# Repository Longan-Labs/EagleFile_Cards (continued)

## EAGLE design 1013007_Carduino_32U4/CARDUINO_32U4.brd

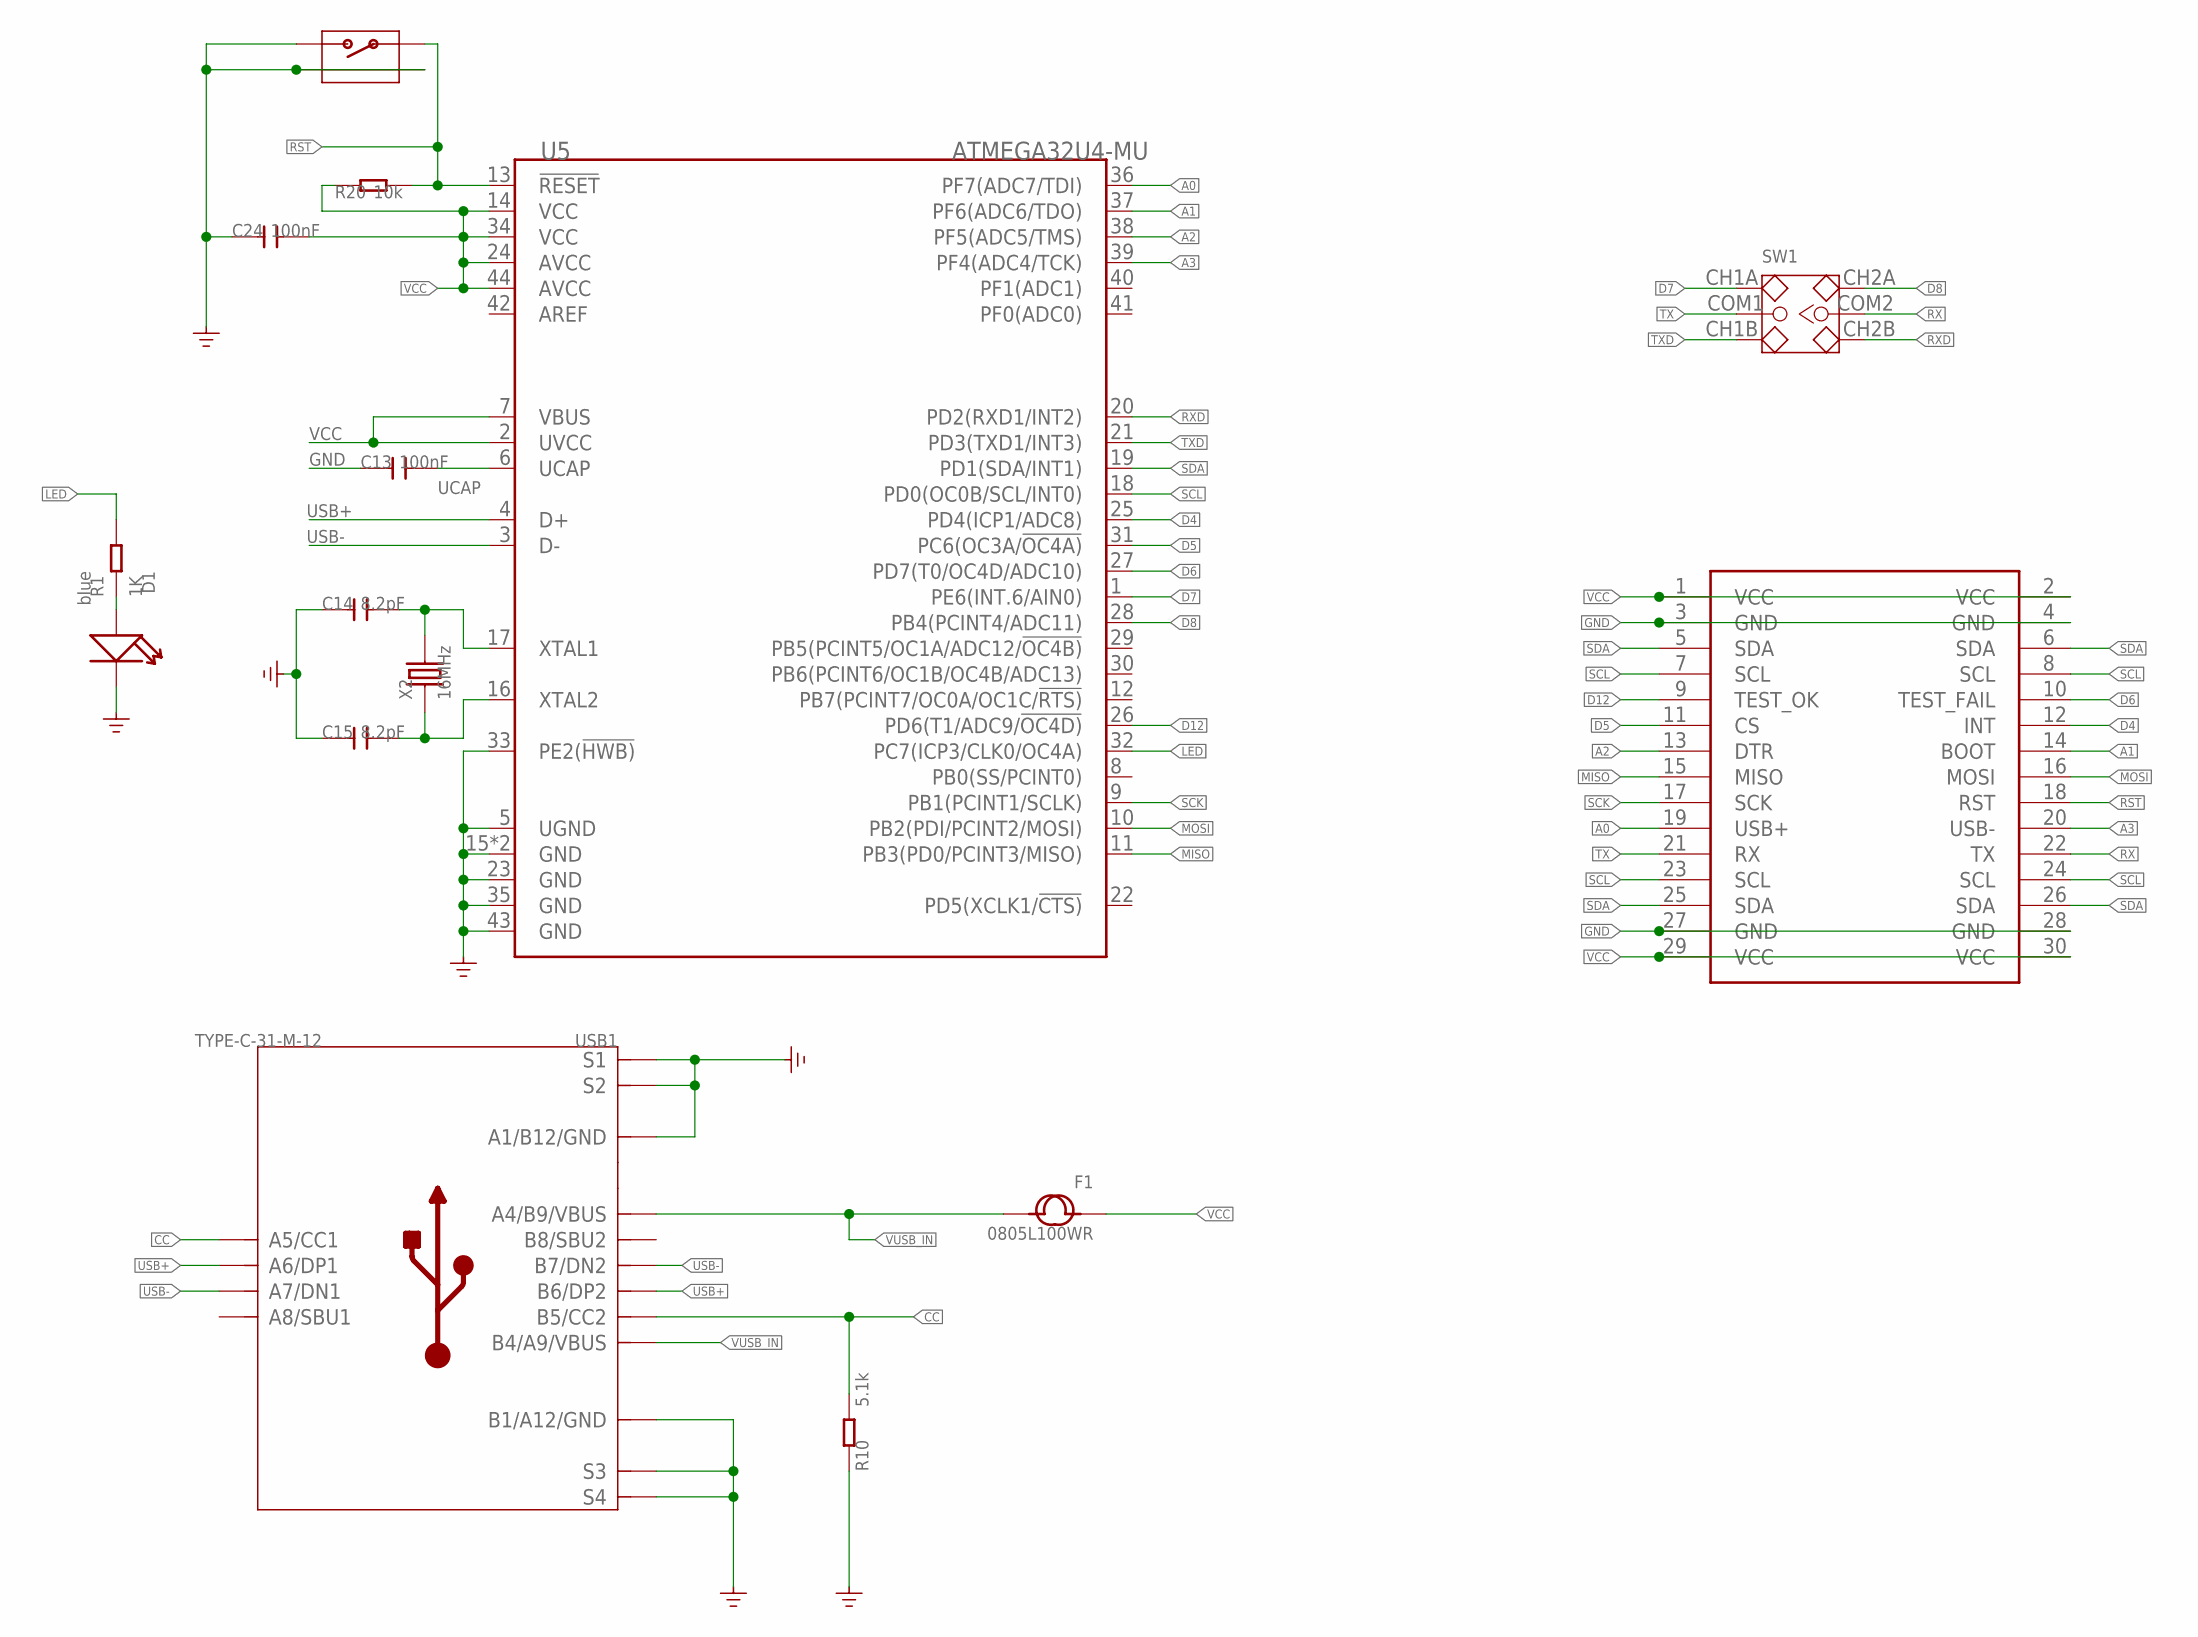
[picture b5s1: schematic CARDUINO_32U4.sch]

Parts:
C13, C24: 100nF; C0603
C14, C15: 8.2pF; C0603
D1: blue; LED-0603
F1: 0805L100WR; F0805
MOUDLE1: MOUDLE-2X15P-2.54'BOARD'; MOUDLE-2X15P-2.54
R1: 1K; R0603
R10: 5.1k; R0603
R20: 10k; R0603
RESET: BUTTON-4P-REINFORCE; 4P-SMD-7X3.5X3.5H
SW1: SWITCH-2CH-6P; SW6-2.5-SMD-9.2X3.5X3.5MM
U5: ATMEGA32U4-MU; QFN44
USB1: TYPE-C-31-M-12; USB2.0-TYPE-C
X2: 16MHz; 2P-SMD-5X3.2

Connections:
A0: MOUDLE1.19 (USB+), U5.36 (PF7(ADC7/TDI))
A1: MOUDLE1.14 (BOOT), U5.37 (PF6(ADC6/TDO))
A2: MOUDLE1.13 (DTR), U5.38 (PF5(ADC5/TMS))
A3: MOUDLE1.20 (USB-), U5.39 (PF4(ADC4/TCK))
CC: R10.2, USB1.A5 (A5/CC1), USB1.B5 (B5/CC2)
D4: MOUDLE1.12 (INT), U5.25 (PD4(ICP1/ADC8))
D5: MOUDLE1.11 (CS), U5.31 (PC6(OC3A/!OC4A))
D6: MOUDLE1.10 (TEST_FAIL), U5.27 (PD7(T0/OC4D/ADC10))
D7: SW1.CH1A, U5.1 (PE6(INT.6/AIN0))
D8: SW1.CH2A, U5.28 (PB4(PCINT4/ADC11))
D12: MOUDLE1.9 (TEST_OK), U5.26 (PD6(T1/ADC9/!OC4D))
GND: C13.1, C14.1, C15.1, C24.1, D1.-, MOUDLE1.3 (GND), MOUDLE1.4 (GND), MOUDLE1.27 (GND), MOUDLE1.28 (GND), R10.1, RESET.2, RESET.S1, RESET.S2, U5.5 (UGND), U5.15 (GND), U5.23 (GND), U5.33 (PE2(!HWB)), U5.35 (GND), U5.43 (GND), U5.TAB (GND), USB1.A1_B12 (A1/B12/GND), USB1.B1_A12 (B1/A12/GND), USB1.S1, USB1.S2, USB1.S3, USB1.S4, USB1.S5 (S1), USB1.S6 (S2)
LED: R1.2, U5.32 (PC7(ICP3/CLK0/OC4A))
MISO: MOUDLE1.15 (MISO), U5.11 (PB3(PD0/PCINT3/MISO))
MOSI: MOUDLE1.16 (MOSI), U5.10 (PB2(PDI/PCINT2/MOSI))
unnamed: D1.+, R1.1
unnamed: C14.2, U5.17 (XTAL1), X2.2
unnamed: C15.2, U5.16 (XTAL2), X2.1
RST: MOUDLE1.18 (RST), R20.2, RESET.1, U5.13 (!RESET)
RX: MOUDLE1.22 (TX), SW1.COM2
RXD: SW1.CH2B, U5.20 (PD2(RXD1/INT2))
SCK: MOUDLE1.17 (SCK), U5.9 (PB1(PCINT1/SCLK))
SCL: MOUDLE1.7 (SCL), MOUDLE1.8 (SCL), MOUDLE1.23 (SCL), MOUDLE1.24 (SCL), U5.18 (PD0(OC0B/SCL/INT0))
SDA: MOUDLE1.5 (SDA), MOUDLE1.6 (SDA), MOUDLE1.25 (SDA), MOUDLE1.26 (SDA), U5.19 (PD1(SDA/INT1))
TX: MOUDLE1.21 (RX), SW1.COM1
TXD: SW1.CH1B, U5.21 (PD3(TXD1/INT3))
UCAP: C13.2, U5.6 (UCAP)
USB+: U5.4 (D+), USB1.A6 (A6/DP1), USB1.B6 (B6/DP2)
USB-: U5.3 (D-), USB1.A7 (A7/DN1), USB1.B7 (B7/DN2)
VCC: C24.2, F1.1, MOUDLE1.1 (VCC), MOUDLE1.2 (VCC), MOUDLE1.29 (VCC), MOUDLE1.30 (VCC), R20.1, U5.2 (UVCC), U5.7 (VBUS), U5.14 (VCC), U5.24 (AVCC), U5.34 (VCC), U5.44 (AVCC)
VUSB_IN: F1.2, USB1.A4_B9 (A4/B9/VBUS), USB1.B4_A9 (B4/A9/VBUS)

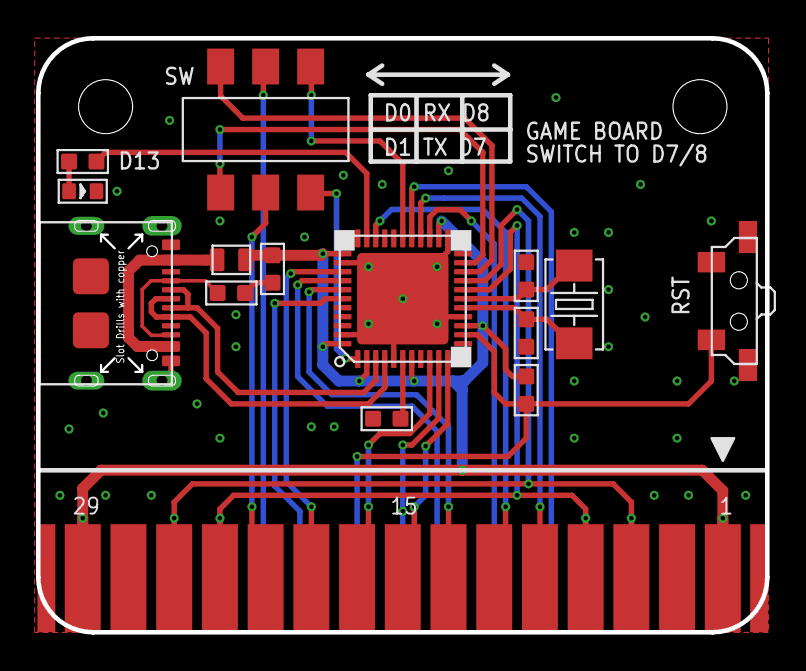
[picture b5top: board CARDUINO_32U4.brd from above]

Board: 2 copper layers, 40.5 x 33.0 mm, 16 parts (1 on the bottom side), 31 nets.

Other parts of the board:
U$6: LONGAN-CARDS-MIDDLE

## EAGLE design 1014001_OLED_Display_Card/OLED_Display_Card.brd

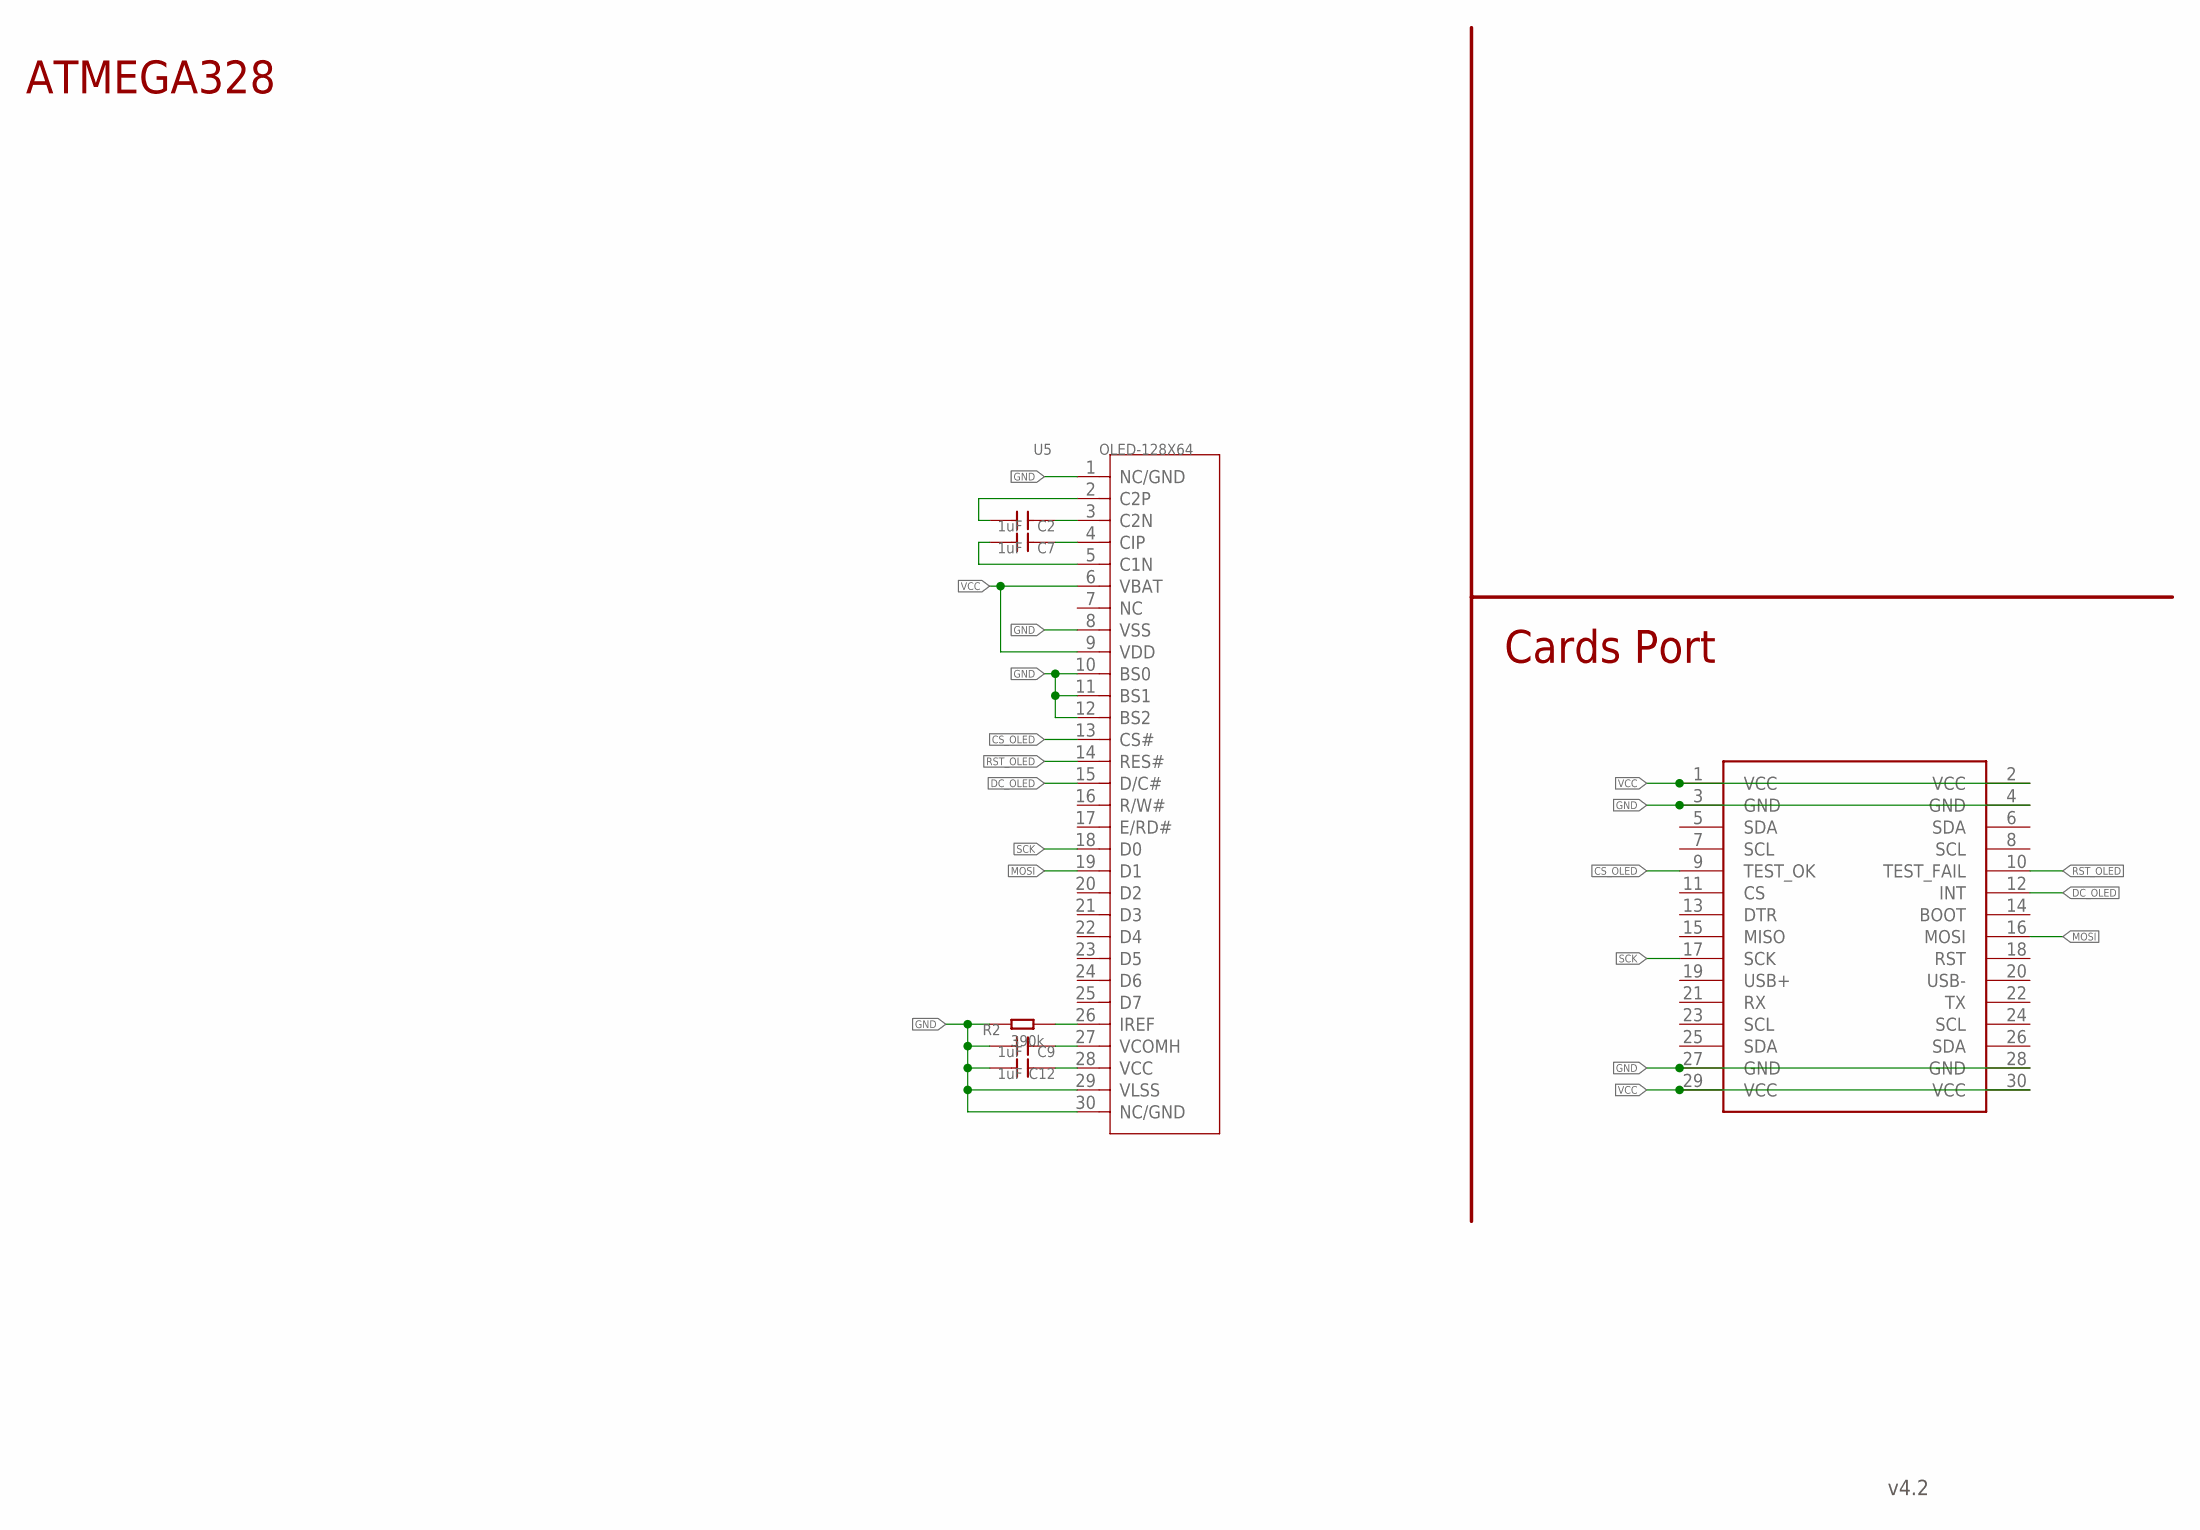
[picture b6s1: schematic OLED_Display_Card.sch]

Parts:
C2, C7, C9, C12: 1uF; C0603@1
MOUDLE1: MOUDLE-2X15P-2.54; MOUDLE-2X15P
R2: 390k; R0603
U5: OLED-128X64; 30P-0.7-34.5X12

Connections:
CS_OLED: MOUDLE1.9 (TEST_OK), U5.13 (CS#)
DC_OLED: MOUDLE1.12 (INT), U5.15 (D/C#)
GND: C9.2, C12.2, MOUDLE1.3 (GND), MOUDLE1.4 (GND), MOUDLE1.27 (GND), MOUDLE1.28 (GND), R2.1, U5.1 (NC/GND), U5.8 (VSS), U5.10 (BS0), U5.11 (BS1), U5.12 (BS2), U5.29 (VLSS), U5.30 (NC/GND)
MOSI: MOUDLE1.16 (MOSI), U5.19 (D1)
unnamed: C2.2, U5.2 (C2P)
unnamed: C2.1, U5.3 (C2N)
unnamed: C7.1, U5.4 (CIP)
unnamed: C7.2, U5.5 (C1N)
unnamed: R2.2, U5.26 (IREF)
unnamed: C12.1, U5.28 (VCC)
unnamed: C9.1, U5.27 (VCOMH)
RST_OLED: MOUDLE1.10 (TEST_FAIL), U5.14 (RES#)
SCK: MOUDLE1.17 (SCK), U5.18 (D0)
VCC: MOUDLE1.1 (VCC), MOUDLE1.2 (VCC), MOUDLE1.29 (VCC), MOUDLE1.30 (VCC), U5.6 (VBAT), U5.9 (VDD)

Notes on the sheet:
v4.2
ATMEGA328
Cards Port

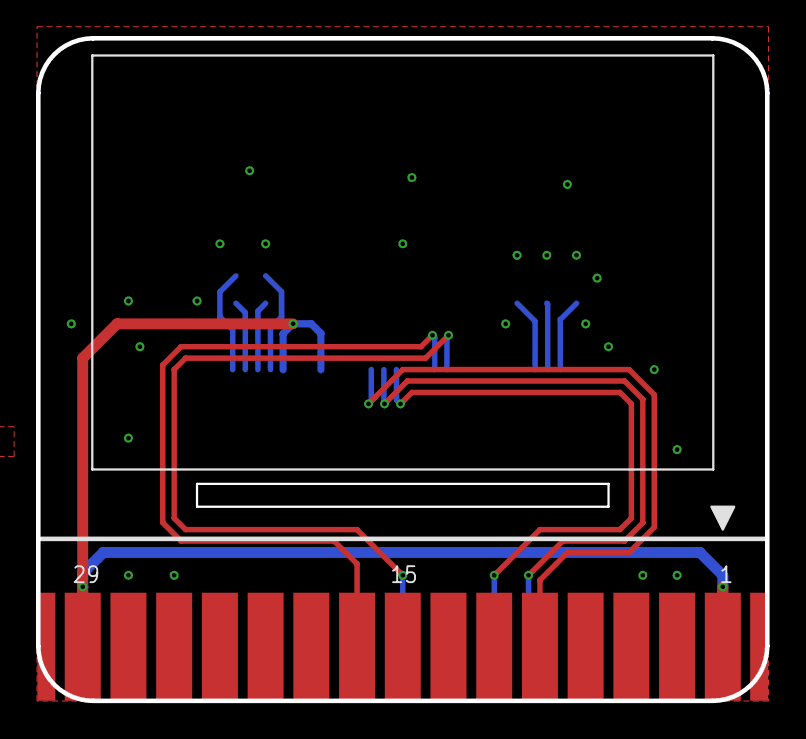
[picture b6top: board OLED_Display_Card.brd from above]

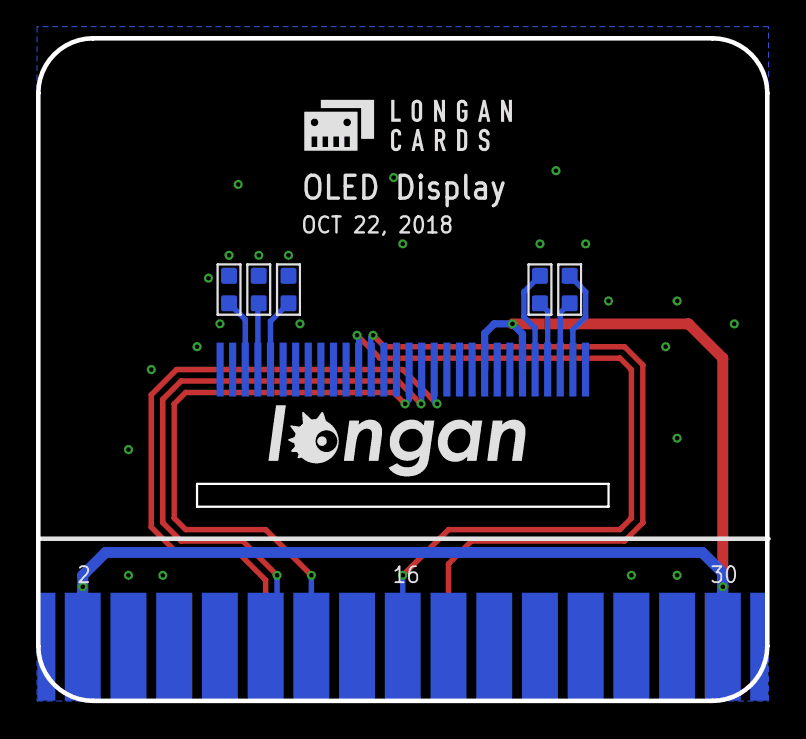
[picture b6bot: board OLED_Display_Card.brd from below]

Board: 2 copper layers, 40.5 x 36.8 mm, 9 parts (7 on the bottom side), 14 nets.

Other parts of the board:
U$1: LONGAN-CARDS-SMALL
U$3: LONGAN-SILK-SMALLER
